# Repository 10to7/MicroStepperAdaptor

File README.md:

MicroStepperAdaptor
===================

A basic adaptor for cheap 2 phase miniature/micro stepper motors

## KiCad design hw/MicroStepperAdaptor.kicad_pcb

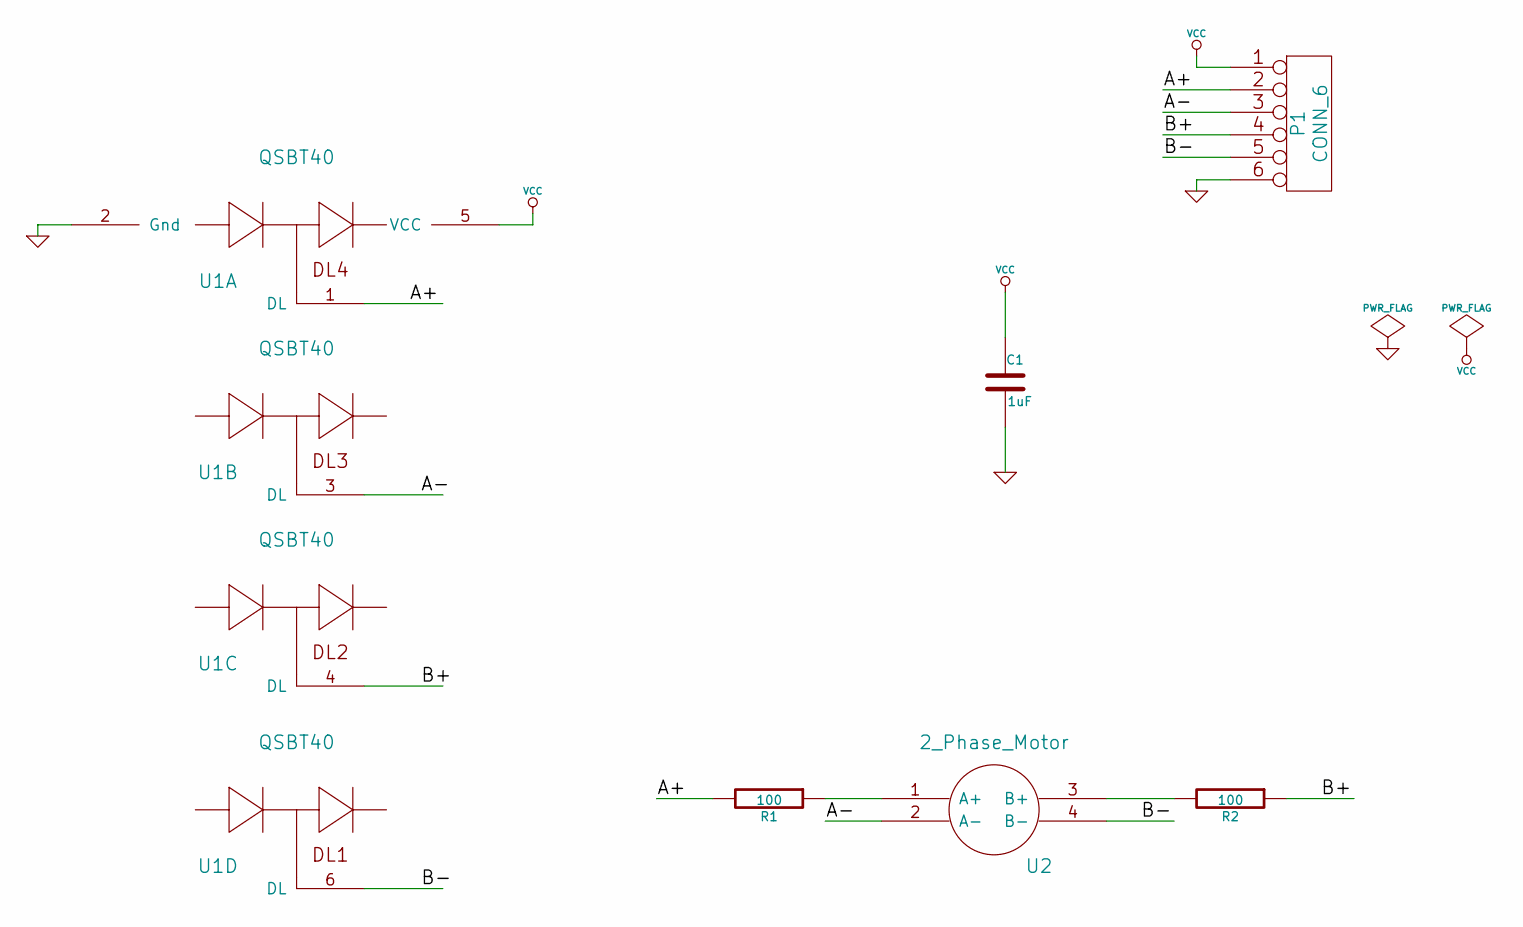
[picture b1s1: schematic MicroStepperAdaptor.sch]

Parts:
C1: 1uF
P1: CONN_6
R1, R2: 100
U1: QSBT40
U2: 2_Phase_Motor

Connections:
/A+: P1.2, R1.2, U1.1 (DL)
/A-: P1.3, U1.3 (DL), U2.2 (A-)
/B+: P1.4, R2.1, U1.4 (DL)
/B-: P1.5, U1.6 (DL), U2.4 (B-)
GND: C1.2, P1.6, U1.2 (Gnd)
unnamed: R1.1, U2.1 (A+)
unnamed: R2.2, U2.3 (B+)
VCC: C1.1, P1.1, U1.5 (VCC)

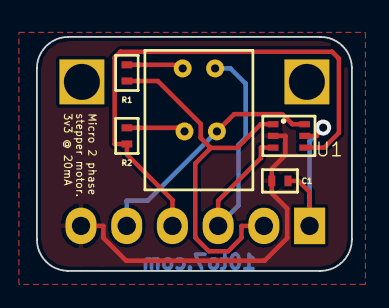
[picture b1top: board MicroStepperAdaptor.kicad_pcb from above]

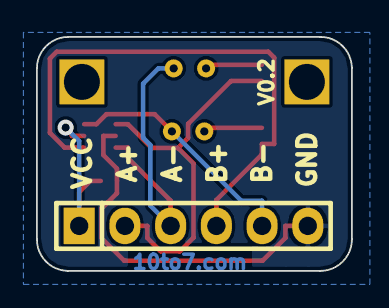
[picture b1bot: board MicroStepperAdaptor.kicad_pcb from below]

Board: 2 copper layers, 17.5 x 13.0 mm, 9 parts (2 on the bottom side), 8 nets.

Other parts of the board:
2mm_Pad_3, 2mm_Pad_4, 2mm_pad_2: VAL**; 2mmHole

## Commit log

2014-05-25 Initially added the breakout board for micro 2 phase stepper motores (Canon?)
2014-06-11 revised stepper motor footprint and reduced the size of the board.
